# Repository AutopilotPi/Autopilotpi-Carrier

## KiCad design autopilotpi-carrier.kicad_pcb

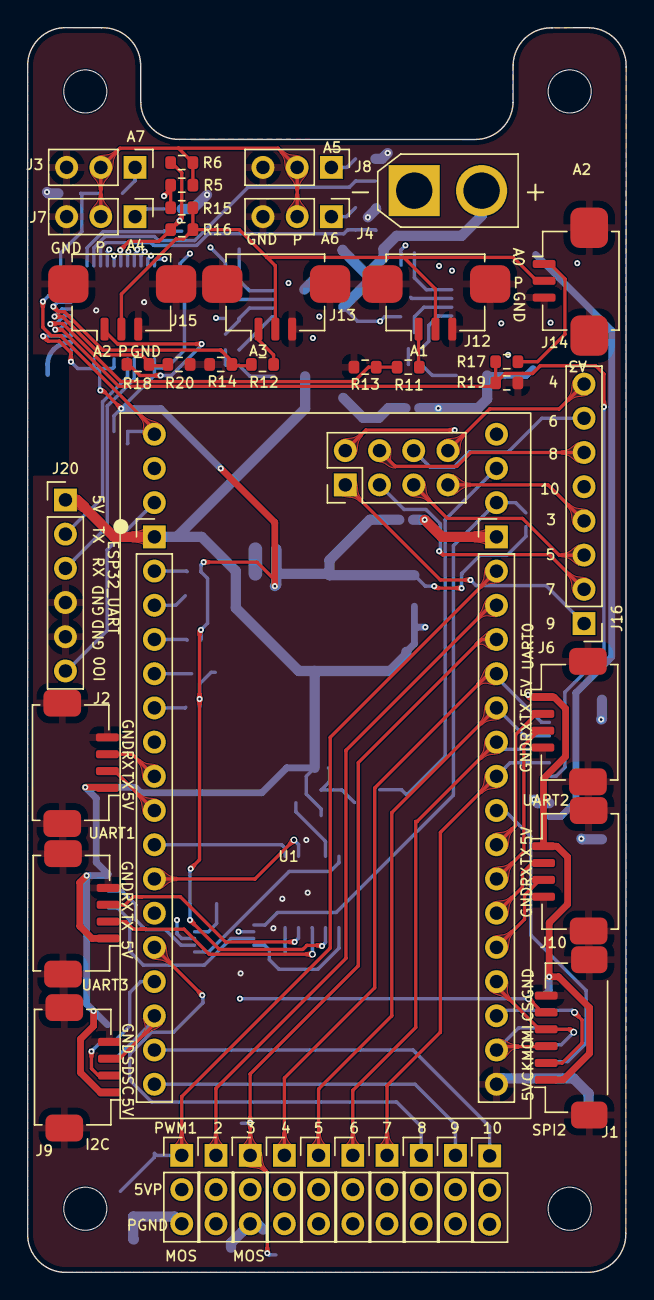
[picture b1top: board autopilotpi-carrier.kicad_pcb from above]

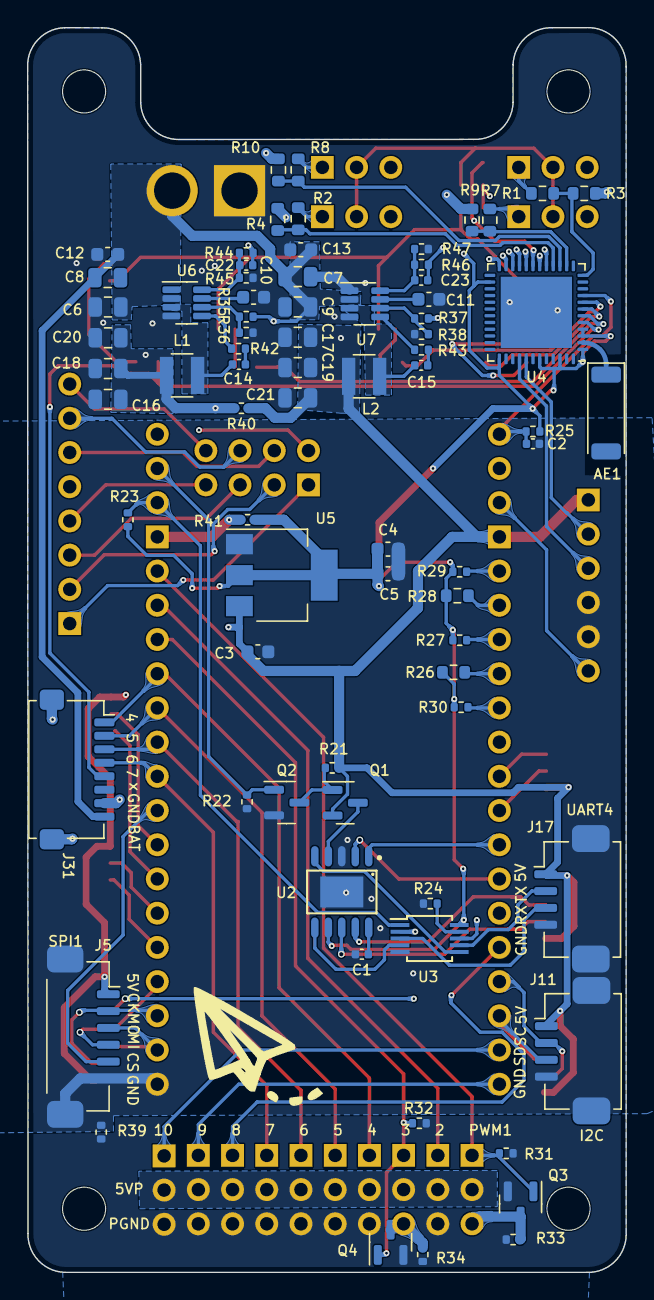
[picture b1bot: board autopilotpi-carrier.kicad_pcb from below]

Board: 4 copper layers, 44.4 x 92.4 mm, 119 parts (75 on the bottom side), 95 nets.

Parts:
AE1: Antenna; Johanson_2450AT43F0100
C1, C2, C14, C15: 0.1uF; C_0402_1005Metric
C3, C4: 10uF; C_0603_1608Metric
C5: 0.1uF; C_0603_1608Metric
C6, C7, C8, C9, C16, C17, C18, C19, C20, C21: 22uF; C_0805_2012Metric
C10, C11, C12, C13: 1uF; C_0603_1608Metric
C22, C23: 220pF; C_0402_1005Metric
H1, H2, H3, H4: MountingHole; MountingHole_3.2mm_M3
J1, J5: Conn_01x06_MountingPin; Molex_CLIK-Mate_502386-0670_1x06-1MP_P1.25mm_Horizontal
J2, J6, J9, J10, J11, J17, J19: Conn_01x04_MountingPin; Molex_CLIK-Mate_502382-0470_1x04-1MP_P1.25mm_Vertical
J3, J4, J7, J8, J21, J22, J23, J24, J25, J26, J27, J28, J29, J30: Conn_01x03; PinHeader_1x03_P2.54mm_Vertical
J12, J13, J14, J15: Conn_01x03_MountingPin; Molex_CLIK-Mate_502382-0370_1x03-1MP_P1.25mm_Vertical
J16: Conn_01x08; PinHeader_1x08_P2.54mm_Vertical
J18: Conn_01x02; AMASS_XT30U-M_1x02_P5.0mm_Vertical
J20: Conn_01x06; PinHeader_1x06_P2.54mm_Vertical
J31: Conn_01x08_MountingPin; Molex_Pico-Clasp_202396-0807_1x08-1MP_P1.00mm_Horizontal
L1, L2: 3.3uH; L_Abracon_ASPI-3012S
Q1: AO3401A; SOT-23
Q2, Q3, Q4: AO3400A; SOT-23
R1, R2, R5, R7, R8, R11, R12, R16, R17, R18: 0R; R_0603_1608Metric
R3, R4, R6, R9, R10, R13, R14, R15, R19, R20, R26, R28: NC; R_0603_1608Metric
R21, R22, R23, R24, R25, R27, R29, R30, R31, R32: 10K; R_0402_1005Metric
R33, R34: short; R_0402_1005Metric
R35, R37: 300K; R_0402_1005Metric
R36, R38: 130K; R_0402_1005Metric
R39: 0R; R_0402_1005Metric
R40, R41: NC; R_0402_1005Metric
R42, R43: 10R; R_0402_1005Metric
R44, R46: 100K; R_0402_1005Metric
R45, R47: 13.7K; R_0402_1005Metric
U1: v3s_flight_controller; Flight_Core
U2: CH342K; SSOP-10_L5.0-W3.9-P1.00-LS6.0-BL-EP
U3: CH442E; MSOP-10_3x3mm_P0.5mm
U4: ESP32-PICO-D4; QFN-48-1EP_7x7mm_P0.5mm_EP5.3x5.3mm
U5: AMS1117-3.3; SOT-223-3_TabPin2
U6, U7: MP2236GJ-P; TSOT-23-8

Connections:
+3.3VP: R41.1, U1.34 (3V3)
+3V3: C4.1, C5.1, R6.1, R16.1, R23.1, R25.1, R26.2, R27.2, R28.2, R29.2, R30.2, R41.2, U2.7 (VIO), U3.10 (VCC), U4.1 (VDDA), U4.3 (VDDA3P3), U4.4 (VDDA3P3), U4.19 (VDD3P3_RTC), U4.26 (VDD_SDIO), U4.37 (VDD3P3_CPU), U4.43 (VDDA), U4.46 (VDDA), U5.2 (VO)
+5V: C3.1, C17.2, C19.2, C21.2, C23.2, J1.1, J2.1, J5.1, J6.1, J9.1, J10.1, J11.1, J17.1, J19.1, J20.1, L2.2, Q1.2 (S), R5.1, R15.1, R21.1, R40.1, R46.2, U1.1 (5V), U5.3 (VI)
+5VP: C16.2, C18.2, C20.2, C22.2, J21.2, J22.2, J23.2, J24.2, J25.2, J26.2, J27.2, J28.2, J29.2, J30.2, L1.2, R40.2, R44.2
+BATT: C6.2, C7.2, C8.2, C9.2, C12.2, C13.2, J18.2, J31.8, R35.2, R37.2, U6.2 (IN), U7.2 (IN)
/ADC0: J31.5, R17.1, R19.2, U4.5 (SENSOR_VP)
/ADC1: R11.1, R13.2, U4.6 (SENSOR_CAPP)
/ADC2: R18.1, R20.2, U4.7 (SENSOR_CAPN)
/ADC3: R12.1, R14.2, U4.8 (SENSOR_VN)
/ADC4: R7.1, R9.2, U4.14 (IO25)
/ADC5: R8.1, R10.2, U4.15 (IO26)
/ADC6: R2.1, R4.2, U4.16 (IO27)
/ADC7: R1.1, R3.2, U4.12 (IO32)
/ADC_PWR1: J3.2, J4.2, J7.2, J8.2, R5.2, R6.2
/ADC_PWR2: J12.2, J13.2, J14.2, J15.2, R15.2, R16.2
/CSN1: J5.5, U1.26 (CSN1)
/CSN2: J1.5, U1.12 (CSN2)
/ESP32_IO0: J20.6, U1.35 (EXT11), U4.23 (IO0)
/ESP32_RX: J20.3, U3.8 (S1C), U4.40 (U0RXD/IO3)
/ESP32_TX: J20.2, U3.2 (S1B), U4.41 (U0TXD/IO1)
/EXT_UART_EN: Q2.1 (G), R22.1, U1.39 (EXT1)
/MISO: J1.4, J5.4, U1.21 (MISO)
/MOSI: J1.3, J5.3, U1.19 (MOSI)
/PWM4: J24.1, J31.1, U1.30 (IO3)
/PWM5: J26.1, J31.2, U1.29 (IO4)
/PWM6: J27.1, J31.3, U1.28 (IO5)
/PWM7: J25.1, J31.4, U1.27 (IO6)
/PWM8: J28.1, U1.13 (IO7)
/PWM9: J29.1, U1.17 (IO8)
/PWM10: J30.1, U1.16 (IO9)
/SCL: J9.2, J11.2, U1.14 (SDA)
/SCLK: J1.2, J5.2, U1.20 (SCK)
/SD1_CLK: U1.7 (SD_CLK), U4.17 (IO14)
/SD1_CMD: R30.1, U1.6 (SD_CMD), U4.21 (IO15)
/SD1_D0: R26.1, U1.5 (SD_D0), U4.22 (IO2)
/SD1_D1: R27.1, U1.4 (SD_D1), U4.24 (IO4)
/SD1_D2: R28.1, U1.3 (SD_D2), U4.18 (IO12)
/SD1_D3: R29.1, U1.2 (SD_D3), U4.20 (IO13)
/SDA: J9.3, J11.3, U1.15 (SCL)
/U0_RX: J6.3, U1.24 (U0_RX)
/U0_TX: J6.2, U1.25 (U0_TX)
/U1_RX: J2.3, U1.8 (U1_RX)
/U1_TX: J2.2, U1.9 (U1_TX)
/U2_RX: J10.3, U1.22 (U2_RX)
/U2_TX: J10.2, U1.23 (U2_TX)
/U3_RX: J19.3, U2.9 (RXD0)
/U3_TX: J19.2, U2.8 (TXD0)
/U4_RX: U2.6 (RXD1), U3.4 (DB)
/U4_RX_OUT: J17.3, U3.3 (S2B)
/U4_TX: U2.5 (TXD1), U3.6 (DC)
/U4_TX_OUT: J17.2, U3.7 (S2C)
/UART4_SW: R23.2, U1.38 (EXT0), U3.1 (IN)
/USB_DN: U1.11 (USB_DN), U2.2 (UD-)
/USB_DP: U1.10 (USB_DP), U2.1 (UD+)
/WENABLE: C2.1, R25.2, U1.37 (EXT13), U4.9 (EN)
/esp32_wifi/ESP32_ANT: AE1.1 (A), U4.2 (LNA_IN)
/power/PWM1: J21.1, Q3.1 (G), R31.2, U1.33 (IO0)
/power/PWM2: J23.1, U1.32 (IO1)
/power/PWM3: J22.1, Q4.1 (G), R32.2, U1.31 (IO2)
GND: C1.2, C2.2, C3.2, C4.2, C5.2, J1.6, J1.MP (MountPin), J2.4, J2.MP (MountPin), J3.3, J4.3, J5.6, J5.MP (MountPin), J6.4, J6.MP (MountPin), J7.3, J8.3, J9.4, J9.MP (MountPin), J10.4, J10.MP (MountPin), J11.4, J11.MP (MountPin), J12.3, J12.MP (MountPin), J13.3, J13.MP (MountPin), J14.3, J14.MP (MountPin), J15.3, J15.MP (MountPin), J17.4, J17.MP (MountPin), J19.4, J19.MP (MountPin), J20.4, J20.5, Q2.2 (S), R3.1, R4.1, R9.1, R10.1, R13.1, R14.1, R19.1, R20.1, R22.2, R24.1, R39.1, U1.18 (GND), U2.3 (GND), U2.11 (GND), U3.5 (GND), U4.49 (GND), U5.1 (GND)
GNDPWR: C6.1, C7.1, C8.1, C9.1, C10.1, C11.1, C12.1, C13.1, C16.1, C17.1, C18.1, C19.1, C20.1, C21.1, J18.1, J23.3, J24.3, J25.3, J26.3, J27.3, J28.3, J29.3, J30.3, J31.7, J31.MP (MountPin), Q3.2 (S), Q4.2 (S), R31.1, R32.1, R33.1, R34.1, R36.1, R38.1, R39.2, R45.1, R47.1, U6.1 (AGND), U6.4 (GND), U7.1 (AGND), U7.4 (GND)
unnamed: C1.1, U2.10 (V3)
unnamed: C10.2, U6.7 (VCC)
unnamed: C11.2, U7.7 (VCC)
unnamed: C14.1, L1.1, U6.3 (SW)
unnamed: C14.2, R42.2
unnamed: C15.1, L2.1, U7.3 (SW)
unnamed: C15.2, R43.2
unnamed: C22.1, R44.1, R45.2, U6.8 (FB)
unnamed: C23.1, R46.1, R47.2, U7.8 (FB)
unnamed: J3.1, R1.2
unnamed: J4.1, R2.2
unnamed: J7.1, R7.2
unnamed: J8.1, R8.2
unnamed: J12.1, R11.2
unnamed: J13.1, R12.2
unnamed: J14.1, R17.2
unnamed: J15.1, R18.2
unnamed: J16.1, U1.41 (EXT9)
unnamed: J16.2, U1.42 (EXT7)
unnamed: J16.3, U1.43 (EXT5)
unnamed: J16.4, U1.44 (EXT3)
unnamed: J16.5, U1.45 (EXT10)
unnamed: J16.6, U1.46 (EXT8)
unnamed: J16.7, U1.47 (EXT6)
unnamed: J16.8, U1.48 (EXT4)
unnamed: J21.3, Q3.3 (D), R33.2
unnamed: J22.3, Q4.3 (D), R34.2
unnamed: Q1.1 (G), Q2.3 (D), R21.2
unnamed: R24.2, U3.9 (EN#)
unnamed: R35.1, R36.2, U6.6 (EN)
unnamed: R37.1, R38.2, U7.6 (EN)
unnamed: R42.1, U6.5 (BST)
unnamed: R43.1, U7.5 (BST)
unnamed: Q1.3 (D), U2.4 (VDD5)

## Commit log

2023-09-23 init.
